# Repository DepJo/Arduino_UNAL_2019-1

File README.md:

# Desarrollo del proyecto final de la asignatura Taller de Electrónica - 2019-1
Dispositivo medidor de temperatura e intensidad de luz, basado en la lectura del sensor DHT11 y una fotorresistencia desde arduino.

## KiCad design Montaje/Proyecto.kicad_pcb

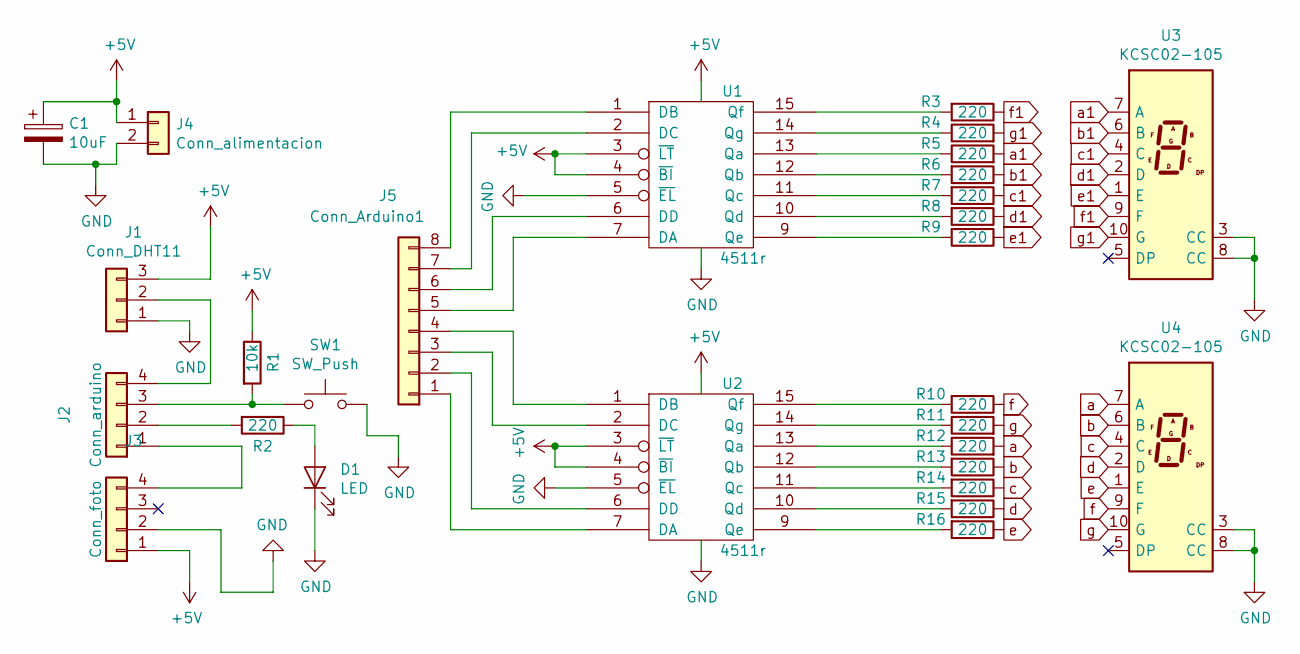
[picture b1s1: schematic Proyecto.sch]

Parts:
C1: 10uF; CP_Radial_D5.0mm_P2.50mm
D1: LED; LED_D3.0mm
J1: Conn_DHT11; PinSocket_1x03_P2.00mm_Horizontal
J2: Conn_arduino; PinHeader_1x04_P2.00mm_Vertical
J3: Conn_foto; PinSocket_1x04_P2.00mm_Horizontal
J4: Conn_alimentacion; PinHeader_1x02_P2.00mm_Vertical
J5: Conn_Arduino1; PinHeader_1x08_P2.00mm_Vertical
R1: 10k; R_Axial_DIN0207_L6.3mm_D2.5mm_P7.62mm_Horizontal
R2, R3, R4, R5, R6, R7, R8, R9, R10, R11, R12, R13, R14, R15, R16: 220; R_Axial_DIN0207_L6.3mm_D2.5mm_P7.62mm_Horizontal
SW1: SW_Push; SW_PUSH_6mm_H5mm
U1, U2: 4511r; DIP-16_W7.62mm_Socket
U3, U4: KCSC02-105; 7SegmentLED_LTS6760_LTS6780

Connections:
+5V: C1.1, J1.3, J3.1, J4.1, R1.1, U1.3 (~LT), U1.4 (~BI), U1.16 (Vdd), U2.3 (~LT), U2.4 (~BI), U2.16 (Vdd)
GND: C1.2, D1.1 (K), J1.1, J3.2, J4.2, SW1.2, U1.5 (~EL), U1.8 (Vss), U2.5 (~EL), U2.8 (Vss), U3.3 (CC), U3.8 (CC), U4.3 (CC), U4.8 (CC)
unnamed: D1.2 (A), R2.1
unnamed: J1.2, J2.4
unnamed: J2.1, J3.4
unnamed: J2.2, R2.2
unnamed: J2.3, R1.2, SW1.1
unnamed: J5.1, U2.7 (DA)
unnamed: J5.2, U2.6 (DD)
unnamed: J5.3, U2.2 (DC)
unnamed: J5.4, U2.1 (DB)
unnamed: J5.5, U1.7 (DA)
unnamed: J5.6, U1.6 (DD)
unnamed: J5.7, U1.2 (DC)
unnamed: J5.8, U1.1 (DB)
unnamed: R3.2, U1.15 (Qf)
unnamed: R4.1, U1.14 (Qg)
unnamed: R5.1, U1.13 (Qa)
unnamed: R6.2, U1.12 (Qb)
unnamed: R7.2, U1.11 (Qc)
unnamed: R8.2, U1.10 (Qd)
unnamed: R9.2, U1.9 (Qe)
unnamed: R10.2, U2.15 (Qf)
unnamed: R11.1, U2.14 (Qg)
unnamed: R12.1, U2.13 (Qa)
unnamed: R13.2, U2.12 (Qb)
unnamed: R14.2, U2.11 (Qc)
unnamed: R15.2, U2.10 (Qd)
unnamed: R16.2, U2.9 (Qe)
a: R12.2, U4.7 (A)
a1: R5.2, U3.7 (A)
b: R13.1, U4.6 (B)
b1: R6.1, U3.6 (B)
c: R14.1, U4.4 (C)
c1: R7.1, U3.4 (C)
d: R15.1, U4.2 (D)
d1: R8.1, U3.2 (D)
e: R16.1, U4.1 (E)
e1: R9.1, U3.1 (E)
f: R10.1, U4.9 (F)
f1: R3.1, U3.9 (F)
g: R11.2, U4.10 (G)
g1: R4.2, U3.10 (G)

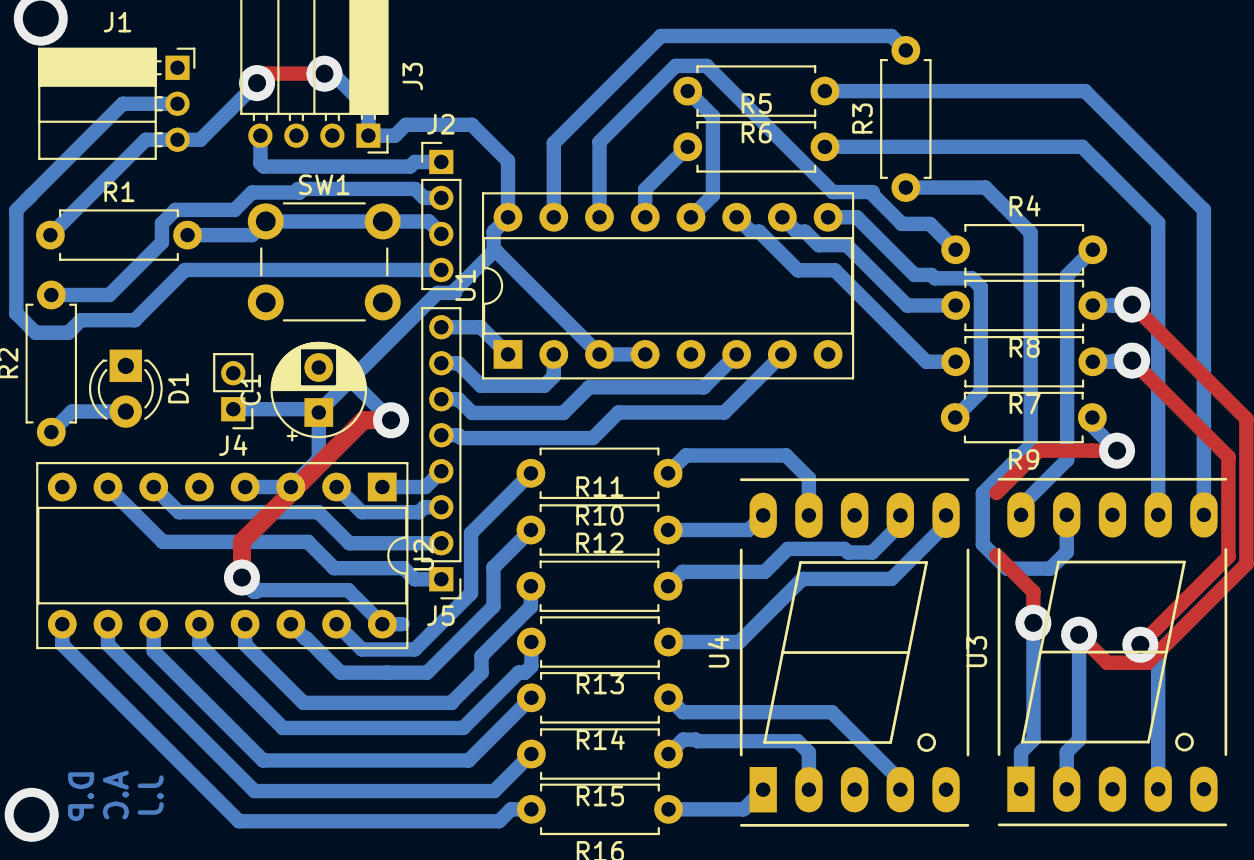
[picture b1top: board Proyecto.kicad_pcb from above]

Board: 2 copper layers, 28 parts (0 on the bottom side), 43 nets.

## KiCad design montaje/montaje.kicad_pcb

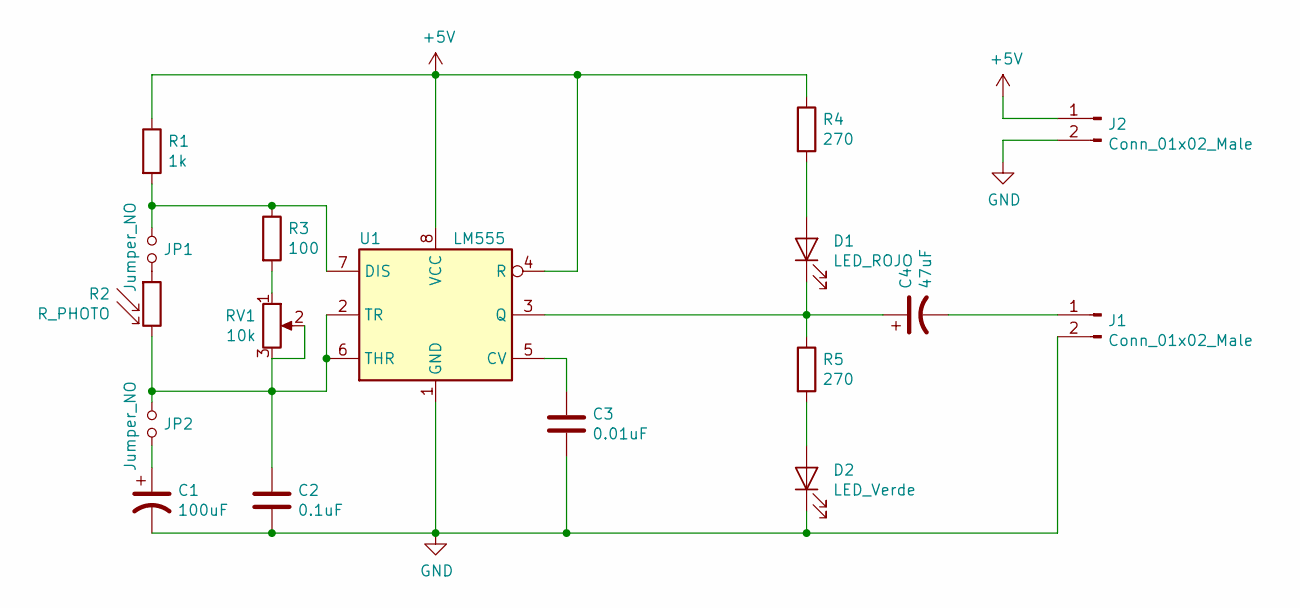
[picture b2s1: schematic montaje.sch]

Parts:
C1: 100uF; CP_Radial_D6.3mm_P2.50mm
C2: 0.1uF; C_Disc_D11.0mm_W5.0mm_P7.50mm
C3: 0.01uF; C_Disc_D7.0mm_W2.5mm_P5.00mm
C4: 47uF; CP_Radial_D5.0mm_P2.50mm
D1: LED_ROJO; LED_D3.0mm_Clear
D2: LED_Verde; LED_D3.0mm_Clear
J1, J2: Conn_01x02_Male; JST_VH_B2P-VH_1x02_P3.96mm_Vertical
JP1, JP2: Jumper_NO; PinHeader_1x02_P1.27mm_Vertical
R1: 1k; R_Axial_DIN0207_L6.3mm_D2.5mm_P10.16mm_Horizontal
R2: R_PHOTO; R_LDR_11x9.4mm_P8.2mm_Vertical
R3: 100; R_Axial_DIN0207_L6.3mm_D2.5mm_P10.16mm_Horizontal
R4, R5: 270; R_Axial_DIN0207_L6.3mm_D2.5mm_P10.16mm_Horizontal
RV1: 10k; Potentiometer_Alps_RK09Y11_Single_Horizontal
U1: LM555; DIP-8_W7.62mm

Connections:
+5V: J2.1, R1.1, R4.1, U1.4 (R), U1.8 (VCC)
GND: C1.2, C2.2, C3.2, D2.1 (K), J1.2, J2.2, U1.1 (GND)
unnamed: C1.1, JP2.2
unnamed: C2.1, JP2.1, R2.2, RV1.2, RV1.3, U1.2 (TR), U1.6 (THR)
unnamed: C3.1, U1.5 (CV)
unnamed: C4.1, D1.1 (K), R5.1, U1.3 (Q)
unnamed: C4.2, J1.1
unnamed: D1.2 (A), R4.2
unnamed: D2.2 (A), R5.2
unnamed: JP1.1, R1.2, R3.1, U1.7 (DIS)
unnamed: JP1.2, R2.1
unnamed: R3.2, RV1.1

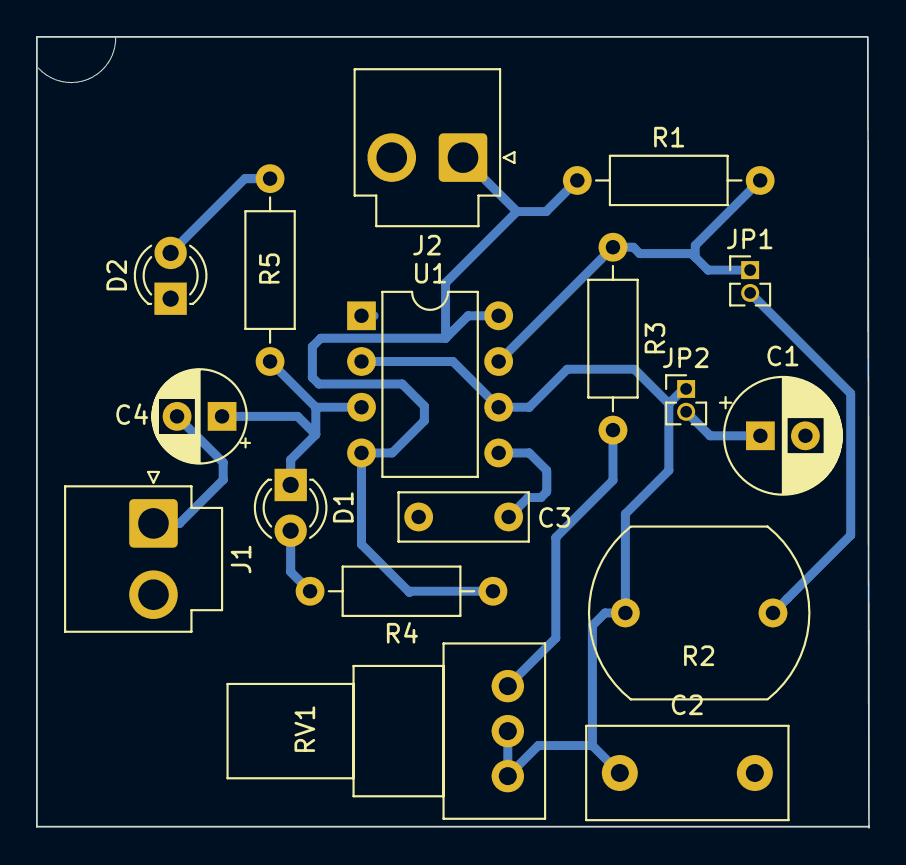
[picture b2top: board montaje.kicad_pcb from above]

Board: 2 copper layers, 46.2 x 43.9 mm, 17 parts (0 on the bottom side), 12 nets.

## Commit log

2023-07-19 Montaje
